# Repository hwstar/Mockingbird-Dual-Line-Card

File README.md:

# Mockingbird-Dual-Lane-Card
A dual subscriber line card for the Mockingbird Telephone Exchange

An interface card design for the Mockingbird Telephone Exchange. 

Features: 
* Provides two subscriber line interfaces.
* STM32F103C8T6 microcontroller.
* Accessed from the Main Microcontroller over I2C
* ATTEN signal to main microcontroller to tell it when there is an event to service.
* Audio bandpass filter for the received audio.
* Uses one R-TONE KS0835 SLIC module for each telephone line interface.
* Analog RX audio output, and TX audio input.
* Designed n KiCAD 8.0.

The main project website is on hackaday.io here: https://hackaday.io/project/196044-mockingbird-telephone-exchange

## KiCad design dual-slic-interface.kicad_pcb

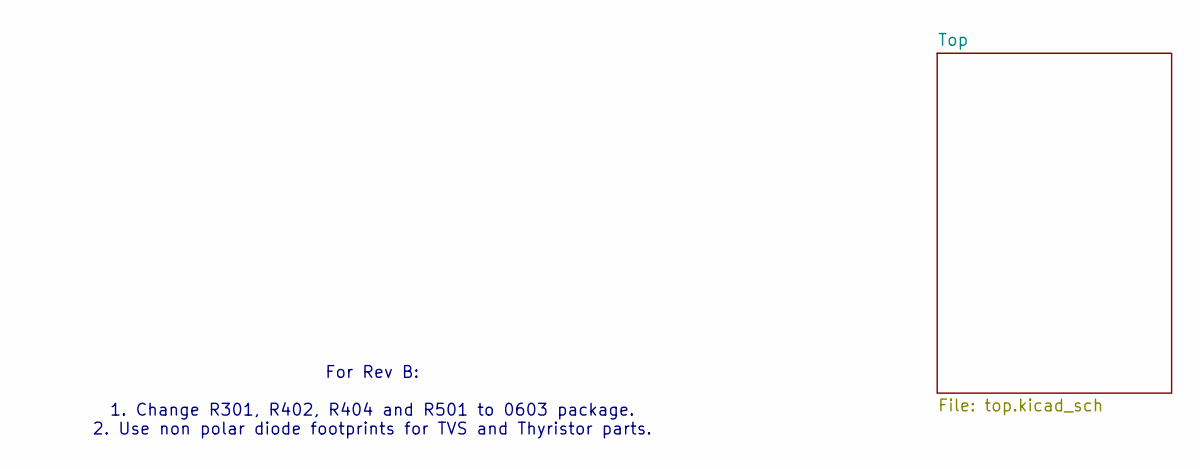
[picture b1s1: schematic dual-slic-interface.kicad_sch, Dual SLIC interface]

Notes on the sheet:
For Rev B: 1. Change R301, R402, R404 and R501 to 0603 package. 2. Use non polar diode footprints for TVS and Thyristor parts.

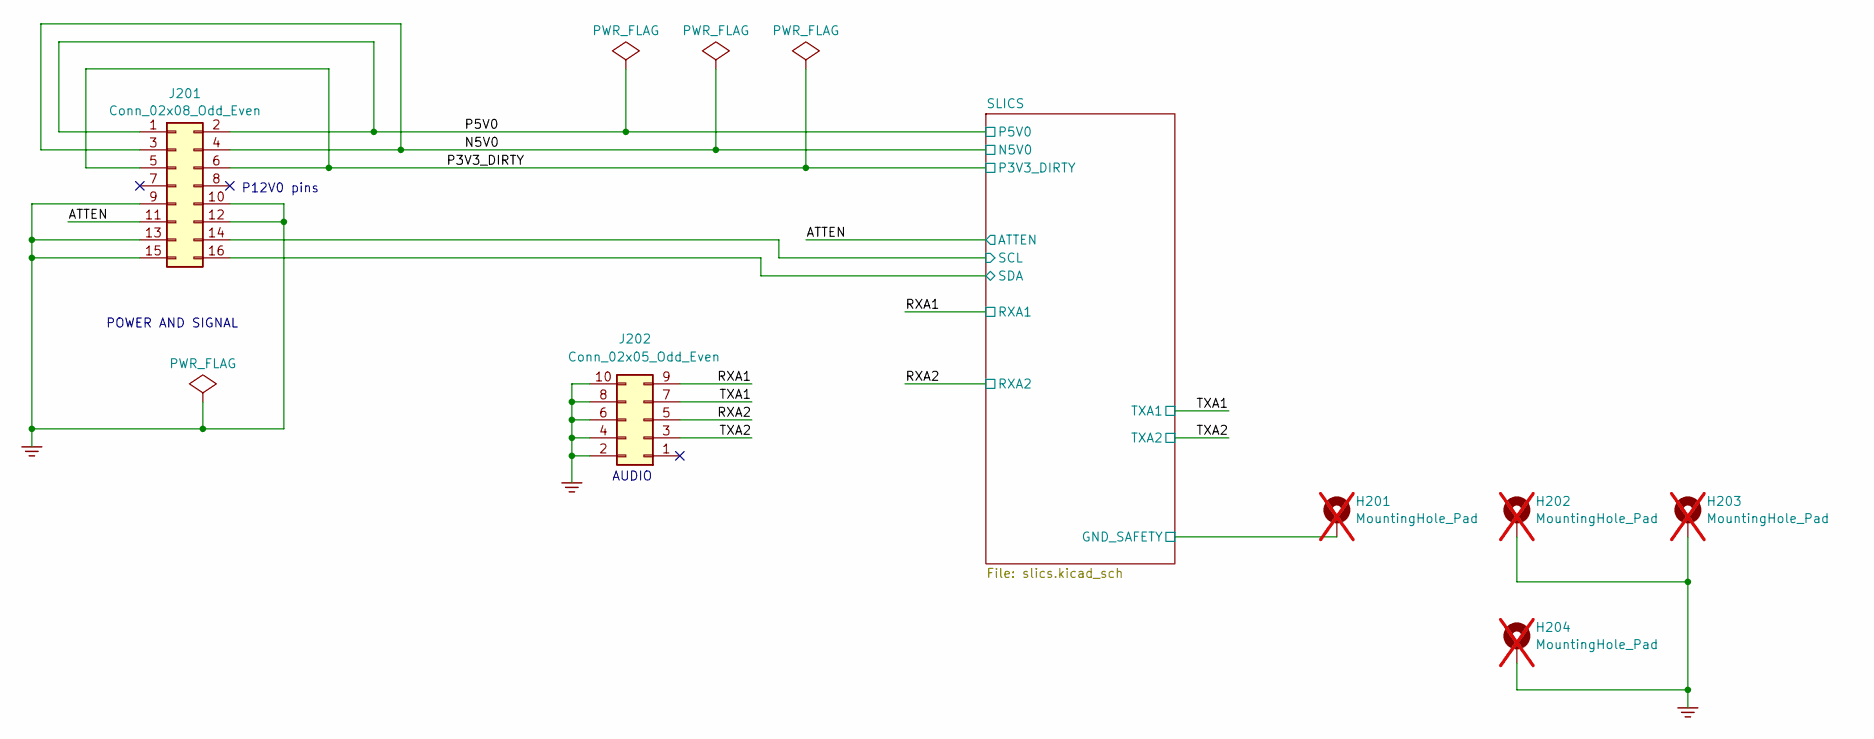
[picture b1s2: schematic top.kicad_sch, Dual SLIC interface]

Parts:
H201, H202, H203, H204: MountingHole_Pad; MountingHole_3.2mm_M3_Pad_Via; PartNumber 800XXX-XXX; not fitted
J201: Conn_02x08_Odd_Even; PinHeader_2x08_P2.54mm_Horizontal; PartNumber 800425-116
J202: Conn_02x05_Odd_Even; PinHeader_2x05_P2.54mm_Horizontal; PartNumber 800425-110

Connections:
/Top/ATTEN: J201.11; also elsewhere on the board
/Top/N5V0: J201.3, J201.4; also elsewhere on the board
/Top/P3V3_DIRTY: J201.5, J201.6; also elsewhere on the board
/Top/P5V0: J201.1, J201.2; also elsewhere on the board
/Top/RXA1: J202.9; also elsewhere on the board
/Top/RXA2: J202.5; also elsewhere on the board
/Top/SLICS/SCL: J201.14; also elsewhere on the board
/Top/SLICS/SDA: J201.16; also elsewhere on the board
/Top/SLICS/slic/GND_SAFETY: H201.1; also elsewhere on the board
/Top/TXA1: J202.7; also elsewhere on the board
/Top/TXA2: J202.3; also elsewhere on the board
GND: H202.1, H203.1, H204.1, J201.9, J201.10, J201.12, J201.13, J201.15, J202.2, J202.4, J202.6, J202.8, J202.10; also elsewhere on the board

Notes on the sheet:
AUDIO
POWER AND SIGNAL
P12V0 pins

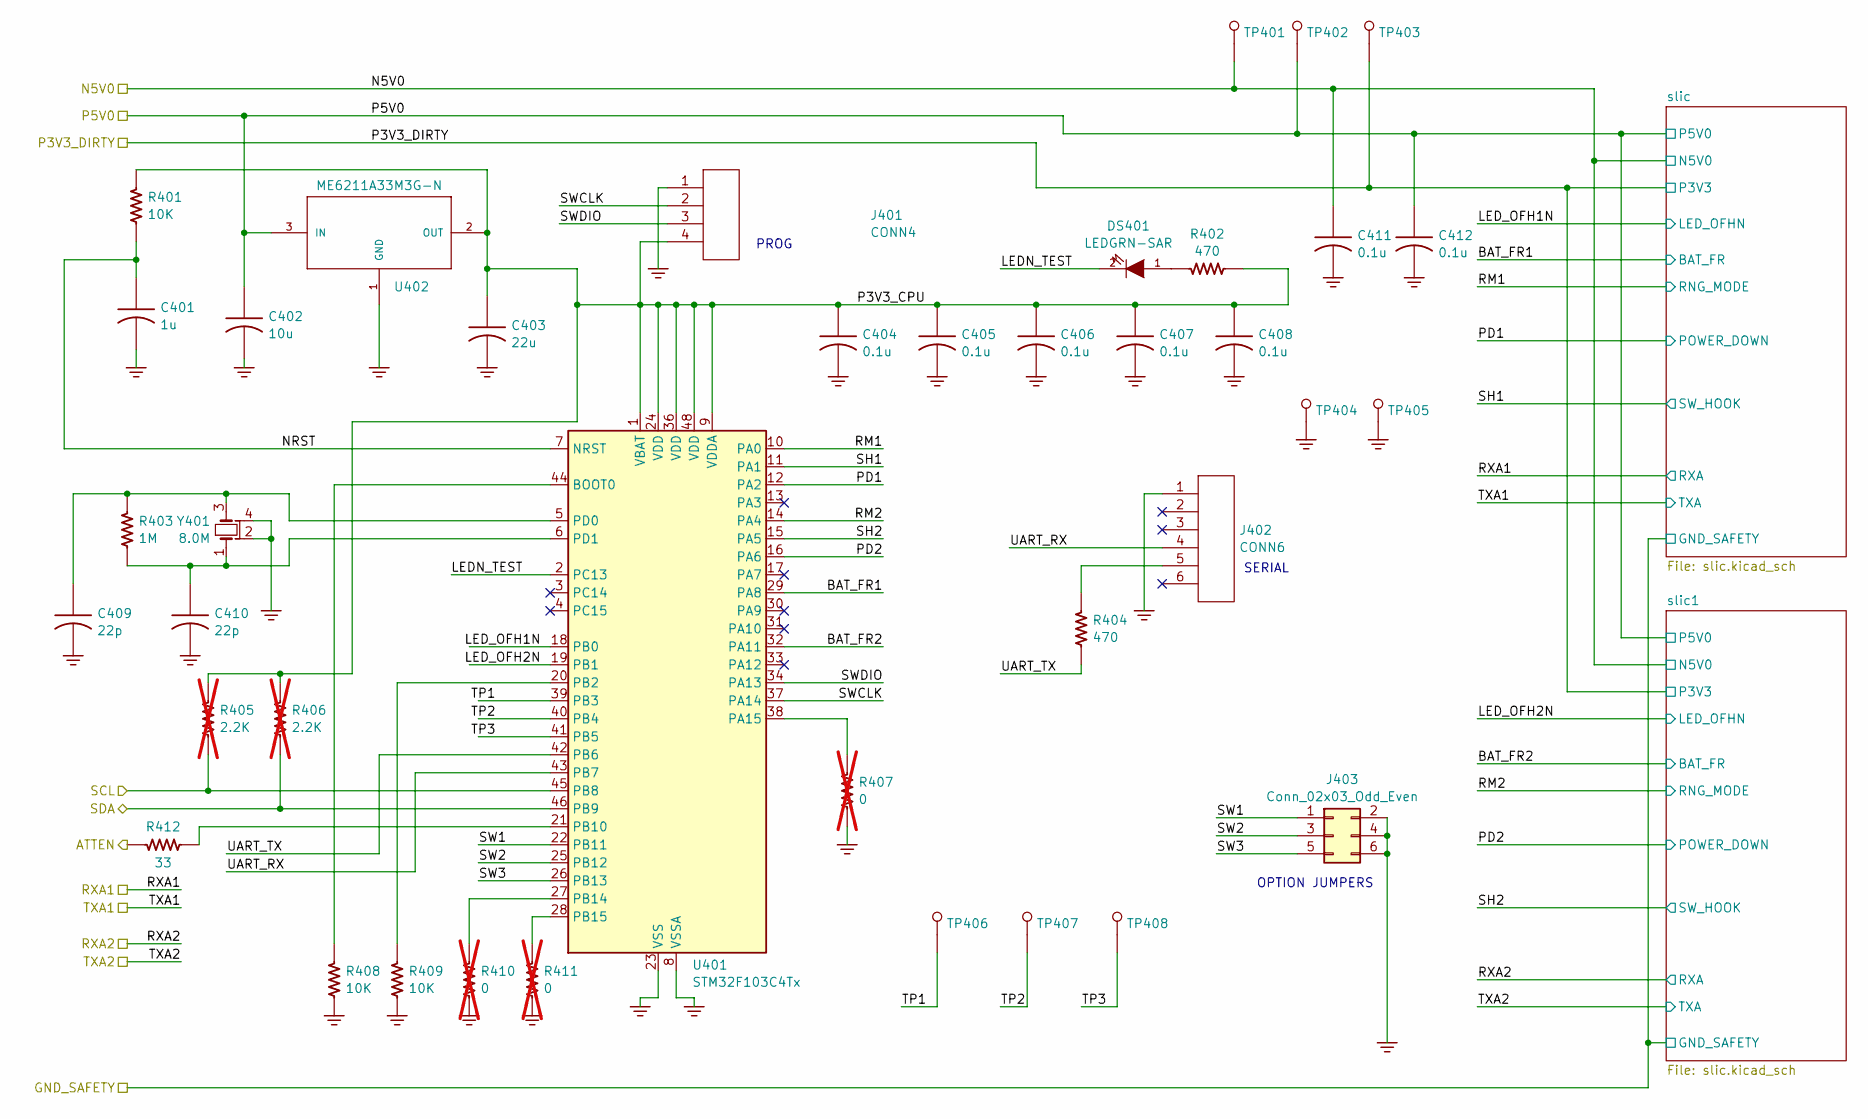
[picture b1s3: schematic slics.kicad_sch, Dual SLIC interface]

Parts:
C401: 1u; C_0805_2012Metric; PartNumber 800238-105
C402: 10u; C_0805_2012Metric; PartNumber 800003-106
C403: 22u; C_0805_2012Metric; PartNumber 800003-226
C404, C405, C406, C407, C408, C411, C412: 0.1u; C_0603_1608Metric; PartNumber 800063-104
C409, C410: 22p; C_0603_1608Metric; PartNumber 800002-220
DS401: LEDGRN-SAR; LED0805; PartNumber 800113-102
J401: CONN4; PinHeader_1x04_P2.54mm_Horizontal; PartNumber 800383-104
J402: CONN6; PinHeader_1x06_P2.54mm_Horizontal; PartNumber 800383-106
J403: Conn_02x03_Odd_Even; PinHeader_2x03_P2.54mm_Horizontal; PartNumber 800425-106
R401, R408, R409: 10K; R_0603_1608Metric; PartNumber 800023-100
R402, R404: 470; R_1206_3216Metric; PartNumber 800057-471
R403: 1M; R_1206_3216Metric; PartNumber 800057-105
R405, R406: 2.2K; R_0603_1608Metric; PartNumber 800022-220; not fitted
R407, R410, R411: 0; R_0603_1608Metric; PartNumber 800020-000; not fitted
R412: 33; R_0603_1608Metric; PartNumber 800020-330
TP401, TP402, TP403, TP404, TP405, TP406, TP407, TP408: TESTPINTPSQ025; TESTPIN
U401: STM32F103C4Tx; LQFP-48_7x7mm_P0.5mm; PartNumber 800405-101
U402: ME6211A33M3G-N; SOT23-3-SAR-V2; PartNumber 800187-101
Y401: 8.0M; Crystal_SMD_3225-4Pin_3.2x2.5mm; PartNumber 800412-008

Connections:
/Top/ATTEN: R412.1; also elsewhere on the board
/Top/N5V0: C411.1, TP401.1 (TP); also elsewhere on the board
/Top/P3V3_DIRTY: TP403.1 (TP); also elsewhere on the board
/Top/P5V0: C402.1, C412.1, TP402.1 (TP), U402.3 (IN); also elsewhere on the board
/Top/SLICS/BAT_FR1: U401.29 (PA8); also elsewhere on the board
/Top/SLICS/BAT_FR2: U401.32 (PA11); also elsewhere on the board
/Top/SLICS/LEDN_TEST: DS401.2 (K), U401.2 (PC13)
/Top/SLICS/LED_OFH1N: U401.18 (PB0); also elsewhere on the board
/Top/SLICS/LED_OFH2N: U401.19 (PB1); also elsewhere on the board
/Top/SLICS/NRST: C401.1, R401.2, U401.7 (NRST)
/Top/SLICS/P3V3_CPU: C403.1, C404.1, C405.1, C406.1, C407.1, C408.1, J401.4, R401.1, R402.2, R405.1, R406.1, U401.1 (VBAT), U401.9 (VDDA), U401.24 (VDD), U401.36 (VDD), U401.48 (VDD), U402.2 (OUT)
/Top/SLICS/PD1: U401.12 (PA2); also elsewhere on the board
/Top/SLICS/PD2: U401.16 (PA6); also elsewhere on the board
/Top/SLICS/RM1: U401.10 (PA0); also elsewhere on the board
/Top/SLICS/RM2: U401.14 (PA4); also elsewhere on the board
/Top/SLICS/SCL: R405.2, U401.45 (PB8); also elsewhere on the board
/Top/SLICS/SDA: R406.2, U401.46 (PB9); also elsewhere on the board
/Top/SLICS/SH1: U401.11 (PA1); also elsewhere on the board
/Top/SLICS/SH2: U401.15 (PA5); also elsewhere on the board
/Top/SLICS/SW1: J403.1, U401.22 (PB11)
/Top/SLICS/SW2: J403.3, U401.25 (PB12)
/Top/SLICS/SW3: J403.5, U401.26 (PB13)
/Top/SLICS/SWCLK: J401.2, U401.37 (PA14)
/Top/SLICS/SWDIO: J401.3, U401.34 (PA13)
/Top/SLICS/TP1: TP406.1 (TP), U401.39 (PB3)
/Top/SLICS/TP2: TP407.1 (TP), U401.40 (PB4)
/Top/SLICS/TP3: TP408.1 (TP), U401.41 (PB5)
/Top/SLICS/UART_RX: J402.4, U401.43 (PB7)
/Top/SLICS/UART_TX: R404.2, U401.42 (PB6)
GND: C401.2, C402.2, C403.2, C404.2, C405.2, C406.2, C407.2, C408.2, C409.2, C410.2, C411.2, C412.2, J401.1, J402.1, J403.2, J403.4, J403.6, R407.2, R408.2, R409.2, R410.2, R411.2, TP404.1 (TP), TP405.1 (TP), U401.8 (VSSA), U401.23 (VSS), U401.35 (VSS), U401.47 (VSS), U402.1 (GND), Y401.2, Y401.4 (2); also elsewhere on the board
unnamed: DS401.1 (A), R402.1
unnamed: J402.5, R404.1
unnamed: R408.1, U401.44 (BOOT0)
unnamed: R407.1, U401.38 (PA15)
unnamed: R409.1, U401.20 (PB2)
unnamed: R412.2, U401.21 (PB10)
unnamed: R410.1, U401.27 (PB14)
unnamed: R411.1, U401.28 (PB15)
unnamed: C409.1, R403.1, U401.5 (PD0), Y401.3
unnamed: C410.1, R403.2, U401.6 (PD1), Y401.1

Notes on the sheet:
SERIAL
OPTION JUMPERS
PROG

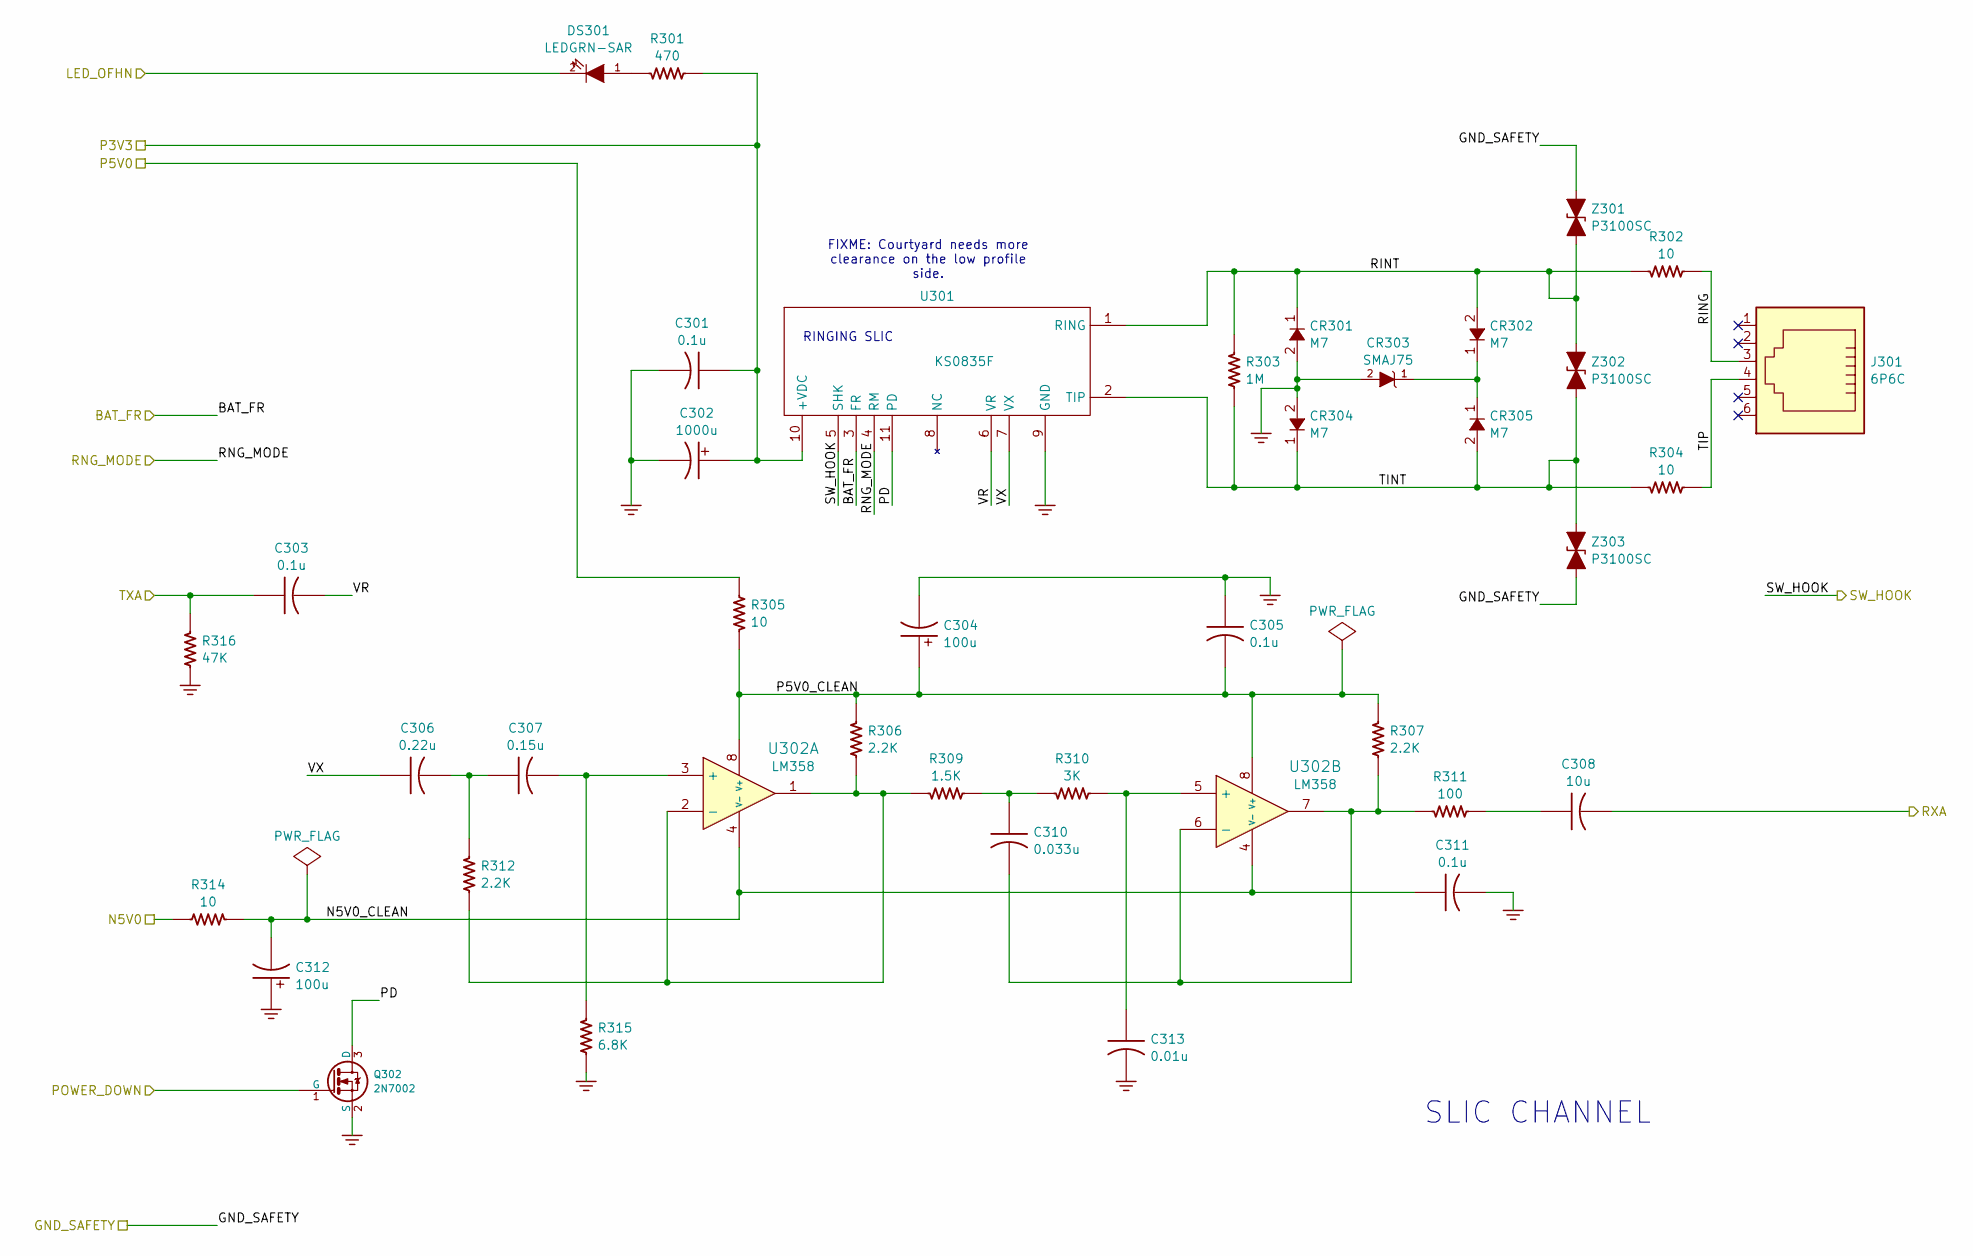
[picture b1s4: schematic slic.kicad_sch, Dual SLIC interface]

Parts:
C301, C303, C305, C311: 0.1u; C_0603_1608Metric; PartNumber 800063-104
C302: 1000u; CP_Elec_8x10.5; PartNumber 800439-108
C304, C312: 100u; CP_Elec_6.3x7.7; PartNumber 800421-107
C306: 0.22u; C_0805_2012Metric; PartNumber 800423-224
C307: 0.15u; C_0603_1608Metric; PartNumber 800422-154
C308: 10u; C_0805_2012Metric; PartNumber 800003-106
C310: 0.033u; C_0603_1608Metric; PartNumber 800422-333
C313: 0.01u; C_0603_1608Metric; PartNumber 800002-103
CR301, CR302, CR304, CR305: M7; D_SMA; PartNumber 800350-101
CR303: SMAJ75; D_SMA; PartNumber 800419-750
DS301: LEDGRN-SAR; LED0805; PartNumber 800113-102
J301: 6P6C; CONN_4P4C_CONNFLY; PartNumber 800417-104
Q302: 2N7002; SOT-23-3; PartNumber 800346-101
R301: 470; R_1206_3216Metric; PartNumber 800057-471
R302, R304, R305, R314: 10; R_1206_3216Metric; PartNumber 800057-100
R303: 1M; R_1206_3216Metric; PartNumber 800057-105
R306, R307, R312: 2.2K; R_0603_1608Metric; PartNumber 800022-220
R309: 1.5K; R_0603_1608Metric; PartNumber 800022-150
R310: 3K; R_0603_1608Metric; PartNumber 800022-300
R311: 100; R_0603_1608Metric; PartNumber 800021-100
R315: 6.8K; R_0603_1608Metric; PartNumber 800022-680
R316: 47K; R_0603_1608Metric; PartNumber 800023-470
U301: KS0835F; SLIC_MODULE_KS0835; PartNumber 800418-101
U302: LM358; SOIC8N-SAR; PartNumber 800379-101
Z301, Z302, Z303: P3100SC; D_SMB; PartNumber 800424-350

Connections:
/Top/N5V0: R314.2; also elsewhere on the board
/Top/P3V3_DIRTY: C301.1, C302.1, R301.2, U301.10 (+VDC); also elsewhere on the board
/Top/P5V0: R305.2; also elsewhere on the board
/Top/RXA1: C308.2; also elsewhere on the board
/Top/SLICS/BAT_FR1: U301.3 (FR); also elsewhere on the board
/Top/SLICS/LED_OFH1N: DS301.2 (K); also elsewhere on the board
/Top/SLICS/PD1: Q302.1 (G); also elsewhere on the board
/Top/SLICS/RM1: U301.4 (RM); also elsewhere on the board
/Top/SLICS/SH1: U301.5 (SHK); also elsewhere on the board
/Top/SLICS/slic/GND_SAFETY: Z301.2 (A2), Z303.1 (A1); also elsewhere on the board
/Top/SLICS/slic/N5V0_CLEAN: C311.1, C312.2, R314.1, U302.4 (V-)
/Top/SLICS/slic/P5V0_CLEAN: C304.1, C305.2, R305.1, R306.1, R307.1, U302.8 (V+)
/Top/SLICS/slic/PD: Q302.3 (D), U301.11 (PD)
/Top/SLICS/slic/RING: J301.3, R302.2
/Top/SLICS/slic/RINT: CR301.1 (K), CR302.2 (A), R302.1, R303.1, U301.1 (RING), Z301.1 (A1), Z302.2 (A2)
/Top/SLICS/slic/TINT: CR304.1 (K), CR305.2 (A), R303.2, R304.1, U301.2 (TIP), Z302.1 (A1), Z303.2 (A2)
/Top/SLICS/slic/TIP: J301.4, R304.2
/Top/SLICS/slic/VR: C303.2, U301.6 (VR)
/Top/SLICS/slic/VX: C306.1, U301.7 (VX)
/Top/TXA1: C303.1, R316.1; also elsewhere on the board
GND: C301.2, C302.2, C304.2, C305.1, C311.2, C312.1, C313.2, CR301.2 (A), CR303.2 (A), CR304.2 (A), Q302.2 (S), R315.2, R316.2, U301.9 (GND); also elsewhere on the board
unnamed: C306.2, C307.1, R312.1
unnamed: C308.1, R311.2
unnamed: C310.1, R309.2, R310.1
unnamed: CR302.1 (K), CR303.1 (K), CR305.1 (K)
unnamed: DS301.1 (A), R301.1
unnamed: C307.2, R315.1, U302.3 (+)
unnamed: R306.2, R309.1, R312.2, U302.1, U302.2 (-)
unnamed: C313.1, R310.2, U302.5 (+)
unnamed: C310.2, R307.2, R311.1, U302.6 (-), U302.7

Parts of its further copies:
C501, C503, C505, C511: 0.1u; C_0603_1608Metric; PartNumber 800063-104
C502: 1000u; CP_Elec_8x10.5; PartNumber 800439-108
C504, C512: 100u; CP_Elec_6.3x7.7; PartNumber 800421-107
C506: 0.22u; C_0805_2012Metric; PartNumber 800423-224
C507: 0.15u; C_0603_1608Metric; PartNumber 800422-154
C508: 10u; C_0805_2012Metric; PartNumber 800003-106
C510: 0.033u; C_0603_1608Metric; PartNumber 800422-333
C513: 0.01u; C_0603_1608Metric; PartNumber 800002-103
CR501, CR502, CR504, CR505: M7; D_SMA; PartNumber 800350-101
CR503: SMAJ75; D_SMA; PartNumber 800419-750
DS501: LEDGRN-SAR; LED0805; PartNumber 800113-102
J501: 6P6C; CONN_4P4C_CONNFLY; PartNumber 800417-104
Q502: 2N7002; SOT-23-3; PartNumber 800346-101
R501: 470; R_1206_3216Metric; PartNumber 800057-471
R502, R504, R505, R514: 10; R_1206_3216Metric; PartNumber 800057-100
R503: 1M; R_1206_3216Metric; PartNumber 800057-105
R506, R507, R512: 2.2K; R_0603_1608Metric; PartNumber 800022-220
R509: 1.5K; R_0603_1608Metric; PartNumber 800022-150
R510: 3K; R_0603_1608Metric; PartNumber 800022-300
R511: 100; R_0603_1608Metric; PartNumber 800021-100
R515: 6.8K; R_0603_1608Metric; PartNumber 800022-680
R516: 47K; R_0603_1608Metric; PartNumber 800023-470
U501: KS0835F; SLIC_MODULE_KS0835; PartNumber 800418-101
U502: LM358; SOIC8N-SAR; PartNumber 800379-101
Z501, Z502, Z503: P3100SC; D_SMB; PartNumber 800424-350

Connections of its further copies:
/Top/N5V0: R514.2; also elsewhere on the board
/Top/P3V3_DIRTY: C501.1, C502.1, R501.2, U501.10 (+VDC); also elsewhere on the board
/Top/P5V0: R505.2; also elsewhere on the board
/Top/RXA2: C508.2; also elsewhere on the board
/Top/SLICS/BAT_FR2: U501.3 (FR); also elsewhere on the board
/Top/SLICS/LED_OFH2N: DS501.2 (K); also elsewhere on the board
/Top/SLICS/PD2: Q502.1 (G); also elsewhere on the board
/Top/SLICS/RM2: U501.4 (RM); also elsewhere on the board
/Top/SLICS/SH2: U501.5 (SHK); also elsewhere on the board
/Top/SLICS/slic1/N5V0_CLEAN: C511.1, C512.2, R514.1, U502.4 (V-)
/Top/SLICS/slic1/P5V0_CLEAN: C504.1, C505.2, R505.1, R506.1, R507.1, U502.8 (V+)
/Top/SLICS/slic1/PD: Q502.3 (D), U501.11 (PD)
/Top/SLICS/slic1/RING: J501.3, R502.2
/Top/SLICS/slic1/RINT: CR501.1 (K), CR502.2 (A), R502.1, R503.1, U501.1 (RING), Z501.1 (A1), Z502.2 (A2)
/Top/SLICS/slic1/TINT: CR504.1 (K), CR505.2 (A), R503.2, R504.1, U501.2 (TIP), Z502.1 (A1), Z503.2 (A2)
/Top/SLICS/slic1/TIP: J501.4, R504.2
/Top/SLICS/slic1/VR: C503.2, U501.6 (VR)
/Top/SLICS/slic1/VX: C506.1, U501.7 (VX)
/Top/SLICS/slic/GND_SAFETY: Z501.2 (A2), Z503.1 (A1); also elsewhere on the board
/Top/TXA2: C503.1, R516.1; also elsewhere on the board
GND: C501.2, C502.2, C504.2, C505.1, C511.2, C512.1, C513.2, CR501.2 (A), CR503.2 (A), CR504.2 (A), Q502.2 (S), R515.2, R516.2, U501.9 (GND); also elsewhere on the board
unnamed: C506.2, C507.1, R512.1
unnamed: C508.1, R511.2
unnamed: C510.1, R509.2, R510.1
unnamed: CR502.1 (K), CR503.1 (K), CR505.1 (K)
unnamed: DS501.1 (A), R501.1
unnamed: C507.2, R515.1, U502.3 (+)
unnamed: R506.2, R509.1, R512.2, U502.1, U502.2 (-)
unnamed: C513.1, R510.2, U502.5 (+)
unnamed: C510.2, R507.2, R511.1, U502.6 (-), U502.7

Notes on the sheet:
SLIC CHANNEL
RINGING SLIC
FIXME: Courtyard needs more clearance on the low profile side.

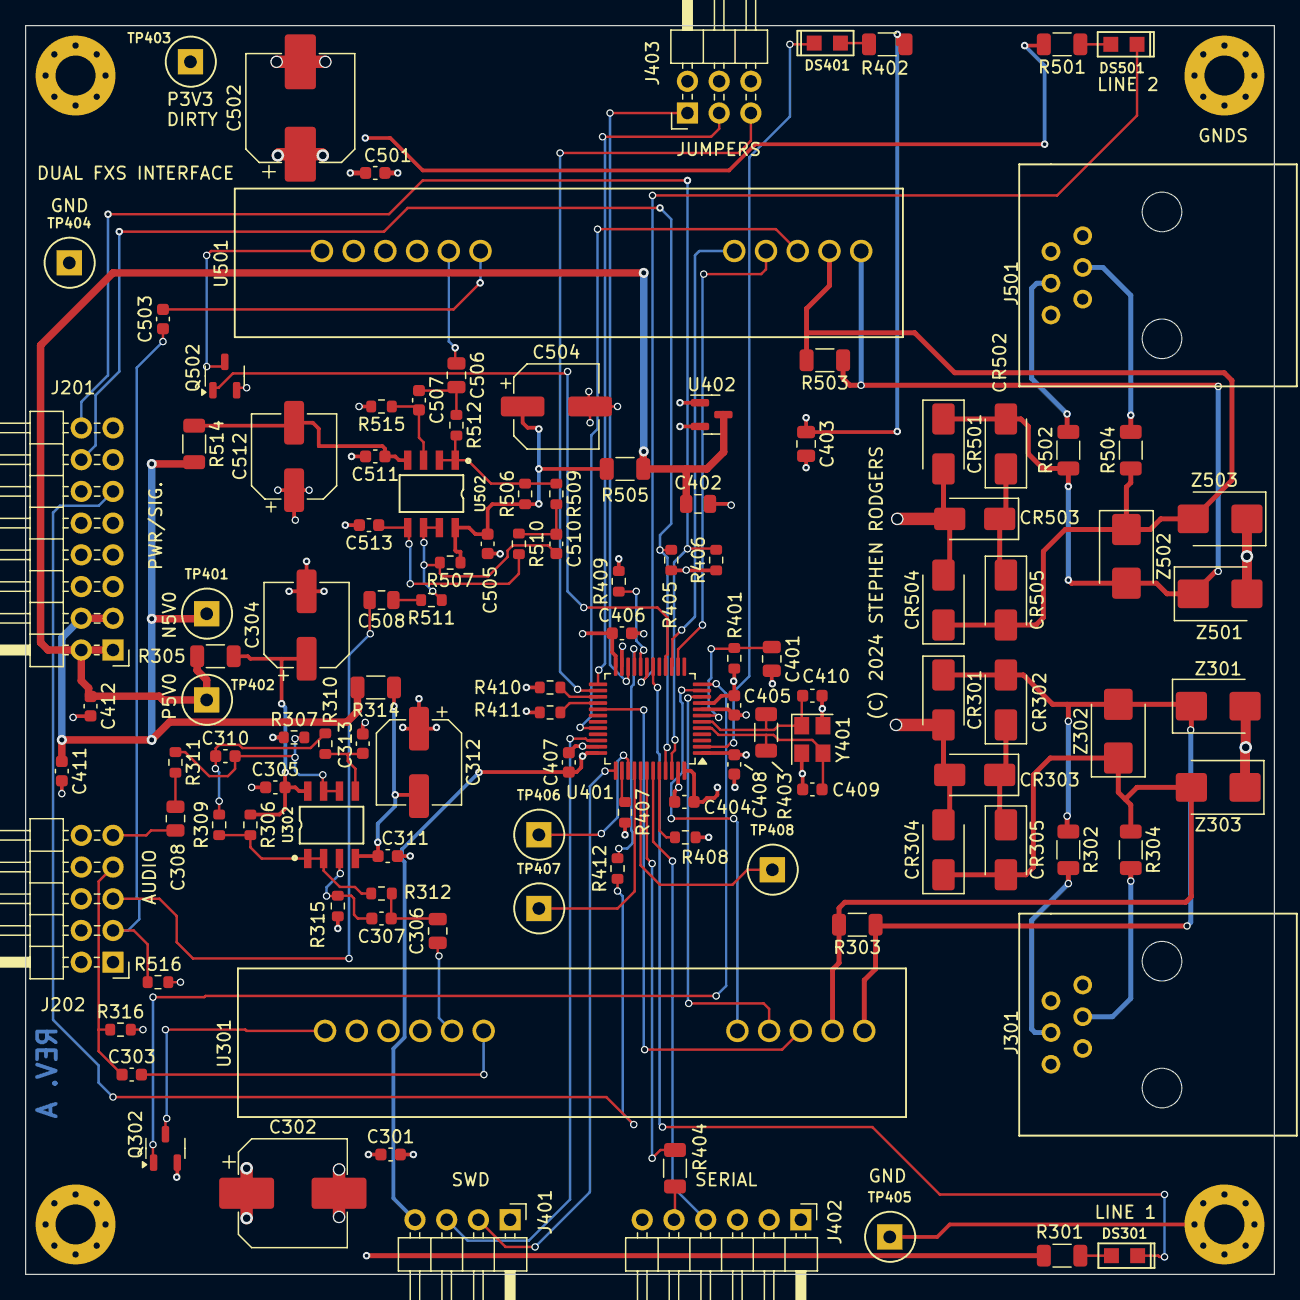
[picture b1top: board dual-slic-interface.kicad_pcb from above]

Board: 4 copper layers, 100.0 x 100.0 mm, 123 parts (0 on the bottom side), 81 nets.

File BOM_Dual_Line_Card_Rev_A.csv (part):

Item,Part Number,Qty,Reference(s),Title/Description,Value on Schematic,Manufacturer,Manufacturer Part Number,Footprint
1,800063-104,15,"C301,C303,C305,C311,C404-C408,C411,C412,C501,C503,C505,C511","CAP,0603,0.1u,50V,X7R",0.1u,Kyocera AVX,06035C104KAT2A,C_0603_1608Metric
1,800063-104,15,"C301,C303,C305,C311,C404-C408,C411,C412,C501,C503,C505,C511","CAP,0603,0.1u,50V,X7R",0.1u,Yageo,CC0603KRX7R9BB104,C_0603_1608Metric
1,800063-104,15,"C301,C303,C305,C311,C404-C408,C411,C412,C501,C503,C505,C511","CAP,0603,0.1u,50V,X7R",0.1u,LCSC,C14663,C_0603_1608Metric
2,800439-108,2,"C302,C502","CAP,ALUM ELECT,1000UF,6.3V,80 MILLIOHM, 8MM",1000u,LCSC,C401739,CP_Elec_8x10.5
2,800439-108,2,"C302,C502","CAP,ALUM ELECT,1000UF,6.3V,80 MILLIOHM, 8MM",1000u,Panasonic,EEEP0J102AP,CP_Elec_8x10.5
3,800421-107,4,"C304,C312,C504,C512","CAP,ALUM_ELECT,100uF,35V,ESR 600mOHM,6.3MM,2000 HR",100u,LCSC,C2836437,CP_Elec_6.3x7.7
3,800421-107,4,"C304,C312,C504,C512","CAP,ALUM_ELECT,100uF,35V,ESR 600mOHM,6.3MM,2000 HR",100u,KNSCHA,RVE100UF35V67RV0072,CP_Elec_6.3x7.7
4,800423-224,2,"C306,C506","CAP,0805,0.22UF,50V,5%,X7R",0.22u,Yageo,CC0805JKX7R9BB224,C_0805_2012Metric
4,800423-224,2,"C306,C506","CAP,0805,0.22UF,50V,5%,X7R",0.22u,LCSC,C520076,C_0805_2012Metric
5,800422-154,2,"C307,C507","CAP,0603,0.15UF,50V,5%,X7R",0.15u,Yageo,CC0603JRX7R9BB154,C_0603_1608Metric
5,800422-154,2,"C307,C507","CAP,0603,0.15UF,50V,5%,X7R",0.15u,LCSC,C519580,C_0603_1608Metric
6,800003-106,3,"C308,C402,C508","CAP,0805,10u,25V,X5R",10u,Murata Electronics,GRM21BR61E106KA73L,C_0805_2012Metric
6,800003-106,3,"C308,C402,C508","CAP,0805,10u,25V,X5R",10u,Samsung Electromechanics,CL21A106KAYNNNE,C_0805_2012Metric
6,800003-106,3,"C308,C402,C508","CAP,0805,10u,25V,X5R",10u,LCSC,C15850,C_0805_2012Metric
7,800422-333,2,"C310,C510","CAP,0603,0.033UF,50V,5%,X7R",0.033u,YAGEO,CC0603JRX7R9BB333,C_0603_1608Metric
7,800422-333,2,"C310,C510","CAP,0603,0.033UF,50V,5%,X7R",0.033u,LCSC,C327162,C_0603_1608Metric
8,800002-103,2,"C313,C513","CAP,0603,0.01u,50V,C0G",0.01u,LCSC,C85973,C_0603_1608Metric
8,800002-103,2,"C313,C513","CAP,0603,0.01u,50V,C0G",0.01u,Murata Electronics,GRM1885C1H103JA01D,C_0603_1608Metric
9,800238-105,1,C401,"CAP,0805,1u,50V,X7R",1u,WALSIN TECH CORP,0805B105K500CT,C_0805_2012Metric
9,800238-105,1,C401,"CAP,0805,1u,50V,X7R",1u,Samsung Electromechanics,CL21B105KBFNNNE,C_0805_2012Metric
9,800238-105,1,C401,"CAP,0805,1u,50V,X7R",1u,LCSC,C28323,C_0805_2012Metric
10,800003-226,1,C403,"CAP,0805,22u,25V,X5R",22u,LCSC,C45783,C_0805_2012Metric
10,800003-226,1,C403,"CAP,0805,22u,25V,X5R",22u,Samsung Electromechanics,CL21A226MAQNNNE,C_0805_2012Metric
11,800002-220,2,"C409,C410","CAP,0603,22p,50V,C0G",22p,LCSC,C1653,C_0603_1608Metric
11,800002-220,2,"C409,C410","CAP,0603,22p,50V,C0G",22p,Samsung Electromechanics,CL10C220JB8NNNC,C_0603_1608Metric
12,800350-101,8,"CR301,CR302,CR304,CR305,CR501,CR502,CR504,CR505","DIODE,RECTIFIER,GP,1A,1KV,SMA",M7,LCSC,C95872,D_SMA
12,800350-101,8,"CR301,CR302,CR304,CR305,CR501,CR502,CR504,CR505","DIODE,RECTIFIER,GP,1A,1KV,SMA",M7,MDD（Microdiode Electronics),M7  ,D_SMA
13,800419-750,2,"CR303,CR503","DIODE,TVS,75V,SMA",SMAJ75,YFW,SMAJ75A,D_SMA
13,800419-750,2,"CR303,CR503","DIODE,TVS,75V,SMA",SMAJ75,LCSC,C2898589,D_SMA
14,800113-102,3,"DS301,DS401,DS501","LED,GREEN,0805",LEDGRN-SAR,LCSC,C434435,LED0805
14,800113-102,3,"DS301,DS401,DS501","LED,GREEN,0805",LEDGRN-SAR,Yongsu Photoelectric,SZYY0805YG,LED0805
15,800425-116,1,J201,"CONN,HDR,STRIP,DUAL ROW,RA,PTH,2X8,0.254 MM PITCH",Conn_02x08_Odd_Even,LCSC,C2935940,PinHeader_2x08_P2.54mm_Horizontal
15,800425-116,1,J201,"CONN,HDR,STRIP,DUAL ROW,RA,PTH,2X8,0.254 MM PITCH",Conn_02x08_Odd_Even,DEALON,DZ254W-22-16-69,PinHeader_2x08_P2.54mm_Horizontal
16,800425-110,1,J202,"CONN,HDR,STRIP,DUAL ROW,RA,PTH,2X5,0.254 MM PITCH",Conn_02x05_Odd_Even,LCSC,C2935937,PinHeader_2x05_P2.54mm_Horizontal
16,800425-110,1,J202,"CONN,HDR,STRIP,DUAL ROW,RA,PTH,2X5,0.254 MM PITCH",Conn_02x05_Odd_Even,DEALON,DZ254W-22-10-69,PinHeader_2x05_P2.54mm_Horizontal
17,800417-104,2,"J301,J501",CONN_4P4C_CONNFLY,6P6C,Connfly,DS1133-01-S60BPS,CONN_4P4C_CONNFLY
17,800417-104,2,"J301,J501",CONN_4P4C_CONNFLY,6P6C,LCSC,C77854,CONN_4P4C_CONNFLY
18,800383-104,1,J401,"HEADER,STRIP,RA,4 POS,0.254MM PITCH",CONN4,DEALON,DZ254W-11-04-65,PinHeader_1x04_P2.54mm_Horizontal
18,800383-104,1,J401,"HEADER,STRIP,RA,4 POS,0.254MM PITCH",CONN4,LCSC,C2935929,PinHeader_1x04_P2.54mm_Horizontal
19,800383-106,1,J402,"HEADER,STRIP,RA,6 POS,0.254MM PITCH",CONN6,LCSC,C2935931,PinHeader_1x06_P2.54mm_Horizontal
19,800383-106,1,J402,"HEADER,STRIP,RA,6 POS,0.254MM PITCH",CONN6,DEALON,DZ254W-11-06-65,PinHeader_1x06_P2.54mm_Horizontal
20,800425-106,1,J403,"CONN,HDR,STRIP,DUAL ROW,RA,PTH,2X3,0.254 MM PITCH",Conn_02x03_Odd_Even,LCSC,C2935935,PinHeader_2x03_P2.54mm_Horizontal
20,800425-106,1,J403,"CONN,HDR,STRIP,DUAL ROW,RA,PTH,2X3,0.254 MM PITCH",Conn_02x03_Odd_Even,DEALON,DZ254W-22-06-69,PinHeader_2x03_P2.54mm_Horizontal
21,800346-101,2,"Q302,Q502","XSTR,MOSFET,SOT-23,N-CH,60V,115MA",2N7002,LCSC,C8545,SOT-23-3
21,800346-101,2,"Q302,Q502","XSTR,MOSFET,SOT-23,N-CH,60V,115MA",2N7002,JIANGSU CHANGJIANG ELECTRONICS TECHNOLOGY CO LTD.,2N7002,SOT-23-3
22,800057-471,4,"R301,R402,R404,R501","RES,1206,470 OHM,1%,1/4W",470,LCSC,C4502,R_1206_3216Metric
22,800057-471,4,"R301,R402,R404,R501","RES,1206,470 OHM,1%,1/4W",470,Uni-Royal,1206W4F4700T5E,R_1206_3216Metric
23,800057-100,8,"R302,R304,R305,R314,R502,R504,R505,R514","RES,1206,10 OHM,1%,1/4W",10,LCSC,C844016,R_1206_3216Metric
23,800057-100,8,"R302,R304,R305,R314,R502,R504,R505,R514","RES,1206,10 OHM,1%,1/4W",10,Vishay,CRCW120610R0FKEB,R_1206_3216Metric
24,800057-105,3,"R303,R403,R503","RES,1206,1M OHM,1%,1/4W",1M,Uni-Royal,1206W4F1004T5E,R_1206_3216Metric
24,800057-105,3,"R303,R403,R503","RES,1206,1M OHM,1%,1/4W",1M,LCSC,C17927,R_1206_3216Metric
25,800022-220,6,"R306,R307,R312,R506,R507,R512","RES,0603,2.2K OHM,1%",2.2K,LCSC,C4190,R_0603_1608Metric
25,800022-220,6,"R306,R307,R312,R506,R507,R512","RES,0603,2.2K OHM,1%",2.2K,Uni-Royal,0603WAF2201T5E,R_0603_1608Metric
26,800022-150,2,"R309,R509","RES,0603,1.50K OHM,1%,E24",1.5K,LCSC,C25804,R_0603_1608Metric
26,800022-150,2,"R309,R509","RES,0603,1.50K OHM,1%,E24",1.5K,Uni-Royal,0603WAF1002T5E,R_0603_1608Metric
27,800022-300,2,"R310,R510","RES,0603,3.0K OHM,1%,E24",3K,Resistor.Today,AECR0603F3K00K9,R_0603_1608Metric
27,800022-300,2,"R310,R510","RES,0603,3.0K OHM,1%,E24",3K,Uni-Royal,0603WAF3001T5E,R_0603_1608Metric
27,800022-300,2,"R310,R510","RES,0603,3.0K OHM,1%,E24",3K,LCSC,C4211,R_0603_1608Metric
28,800021-100,2,"R311,R511","RES,0603,100 OHM,1%",100,LCSC,"C22775,C2759451",R_0603_1608Metric
28,800021-100,2,"R311,R511","RES,0603,100 OHM,1%",100,Uni-Royal,0603WAF1000T5E,R_0603_1608Metric
29,800022-680,2,"R315,R515","RES,0603,6.8K OHM,1%,E24",6.8K,LCSC,C23212,R_0603_1608Metric
29,800022-680,2,"R315,R515","RES,0603,6.8K OHM,1%,E24",6.8K,Uni-Royal,0603WAF6801T5E,R_0603_1608Metric
30,800023-470,2,"R316,R516","RES,0603,47K OHM,1%",47K,LCSC,C25819,R_0603_1608Metric
30,800023-470,2,"R316,R516","RES,0603,47K OHM,1%",47K,Uni-Royal,0603WAF4702T5E,R_0603_1608Metric
31,800023-100,3,"R401,R408,R409","RES,0603,10.0K OHM,1%",10K,WALSIN TECH CORP,MR06X1002FTL,R_0603_1608Metric
31,800023-100,3,"R401,R408,R409","RES,0603,10.0K OHM,1%",10K,Uni-Royal,0603WAF1002T5E,R_0603_1608Metric
31,800023-100,3,"R401,R408,R409","RES,0603,10.0K OHM,1%",10K,LCSC,C25804,R_0603_1608Metric
32,800020-000,3,"R407,R410,R411","RES,0603,0 OHM,1%,E24",0,LCSC,C21189,R_0603_1608Metric
32,800020-000,3,"R407,R410,R411","RES,0603,0 OHM,1%,E24",0,Uni-Royal,0603WAF0000T5E,R_0603_1608Metric
33,800020-330,1,R412,"RES,0603,33 OHM,1%,E24",33,Uni-Royal,0603WAF330JT5E,R_0603_1608Metric
33,800020-330,1,R412,"RES,0603,33 OHM,1%,E24",33,LCSC,C23140,R_0603_1608Metric
34,800418-101,2,"U301,U501","MODULE_SLIC,RINGING",KS0835F,R-TONE,KS0835F,SLIC_MODULE_KS0835
35,800379-101,2,"U302,U502","IC,OP-AMP,GP,DUAL,SOIC8",LM358,LCSC,C7950,SOIC8N-SAR
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
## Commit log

2024-05-19 Remove old file

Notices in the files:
dual-slic-interface.kicad_pcb:
(C) 2024 STEPHEN RODGERS
